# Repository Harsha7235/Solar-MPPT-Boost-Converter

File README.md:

Solar MPPT Boost Converter — 24 V Output
A hardware-oriented solar power conversion project involving the schematic design and PCB layout of an Arduino-assisted boost-converter stage. The design was created in KiCad and is intended to step up a lower DC input from a solar source to a nominal 24 V output.
Project status: Schematic and PCB design/fabrication work completed by the project author. The screenshots show the circuit schematic and routed PCB layout. Do not interpret the nominal output label as proof of a regulated 24 V output under every input/load condition; measured performance data should be added after testing.

Repository name
Solar-MPPT-Boost-Converter
Repository description
KiCad schematic and PCB design for an Arduino-assisted solar MPPT boost-converter prototype with a nominal 24 V output.
Project overview
The project combines a boost-converter power stage with a microcontroller-based control/monitoring arrangement. The visible schematic contains an Arduino Nano, an INA219 current/voltage-monitoring IC, an inductor, a Schottky power diode, a MOSFET switching device, input/output capacitors, and supporting gate/feedback components.

The intended system-level workflow is:
1. Accept a DC input from a solar source.
2. Use a boost power stage to raise the input voltage.
3. Use the Arduino-based control arrangement for the intended MPPT/control logic.
4. Monitor electrical quantities through the INA219 interface.
5. Provide a nominal 24 V output at the output connector.
Important: The supplied screenshots establish the circuit and PCB design elements, but do not show the complete MPPT firmware, a solar-panel test setup, calibration procedure, closed-loop control results, or measured efficiency. Add those details only when they are implemented and verified.
Hardware visible in the schematic
Reference / component	Value or part marking shown	Intended role
A1	Arduino Nano (V3.x footprint)	Microcontroller platform for control and monitoring
U1	INA219AD	I²C-based voltage/current/power monitoring
L1	220 µH	Boost-converter energy-storage inductor
D1	MBR1060	Schottky rectifier in the boost power stage
Q1	P30N06L	MOSFET switching device
C1, C2	470 µF	Bulk input/output filtering capacitors (confirm exact net placement from the schematic)
C3, C4	100 nF	High-frequency bypass/decoupling capacitors
R1	10 Ω	Gate-series resistor as drawn
R2	100 kΩ	Gate pull-down resistor as drawn
J1	2-pin connector	Input connection as labelled in the schematic
J2	2-pin connector	Output connection labelled VOUT_24V / GND
J3	2-pin connector	Additional board connection; verify its final intended use from the netlist

Part numbers and values above are transcribed from the provided schematic image. Confirm the exact manufacturer datasheets, pinouts, voltage/current ratings, capacitor polarity, and connector functions before applying power.
Design files
Upload the native KiCad project files to this repository so that the design can be inspected and edited:
- *.kicad_pro — KiCad project
- *.kicad_sch — schematic
- *.kicad_pcb — PCB layout
- fabrication/ — Gerber files, drill files, and fabrication notes (if generated)
- images/ — schematic and PCB screenshots
- firmware/ — Arduino source code (if available)
The screenshots alone are not a substitute for the editable KiCad source files or manufacturing outputs.
Design workflow
1. Schematic capture: Place the power-stage, sensing, controller, passive components, and connectors in KiCad.
2. Electrical connections: Connect the boost stage, sensing interface, controller pins, input, and output nets.
3. PCB placement: Arrange the components on the board while considering power-path length, switching-node area, grounding, and component accessibility.
4. Routing: Route the power and signal connections in the PCB editor. The supplied board image shows routed copper and the component footprints.
5. Fabrication preparation: Generate and inspect Gerber/drill outputs and verify the board against the schematic before manufacturing.
6. Bring-up and testing: Test with a current-limited bench supply and suitable load before connecting a solar panel or valuable equipment.
Power-electronics design considerations
A boost converter can produce an output voltage higher than its input, but the actual output depends on the input range, switching frequency, duty cycle, inductor, diode, MOSFET, load, feedback method, and losses.

For a practical MPPT implementation, document and validate:
- Solar-panel voltage/current operating range.
- MPPT algorithm used (for example, Perturb and Observe or Incremental Conductance), if implemented.
- PWM frequency and duty-cycle limits.
- Voltage/current sensing calibration and sampling rate.
- Output-voltage regulation method and over-voltage protection.
- Input undervoltage, output overcurrent, thermal, and short-circuit protection.
- Inductor saturation current, MOSFET safe operating area, diode rating, capacitor ripple-current rating, and PCB copper-current capacity.
The ideal continuous-conduction boost relationship is:
\[
V_{out} = \frac{V_{in}}{1-D}
\]
where D is the switch duty cycle. This is an ideal relationship, not a measured performance claim; real designs have losses and operating limits.
Safety and validation
This is a switching power-electronics circuit. Incorrect wiring, component polarity, PCB clearance, grounding, or control settings can damage hardware or cause burns/fire.

Before powering the board:
- Check the schematic-to-PCB consistency and run KiCad ERC and PCB DRC.
- Inspect solder joints, component orientation, connector polarity, and MOSFET/diode pinouts.
- Verify there are no shorts between input, output, and ground.
- Confirm the voltage ratings of all capacitors and semiconductors exceed the maximum possible circuit voltage with suitable margin.
- Start with a current-limited bench supply and a dummy load.
- Increase input voltage and load gradually while monitoring the MOSFET, diode, inductor, and capacitors for heating.
- Measure input voltage/current, output voltage/current, ripple, and efficiency before describing the converter as tested or regulated.
Do not connect the board directly to a battery, panel, or load until the design has passed these checks.
Results
The currently supplied project evidence is the KiCad schematic and PCB layout screenshots. Add a measured-results table here after bench testing:
Parameter	Measured result
Solar/DC input voltage range	To be measured
Input current	To be measured
Output voltage under load	To be measured
Output current / load	To be measured
Switching frequency	To be confirmed
Efficiency	To be measured
Output ripple	To be measured
Thermal performance	To be measured

Suggested repository structure
Solar-MPPT-Boost-Converter/
├── README.md
├── kicad/
│   ├── project.kicad_pro
│   ├── project.kicad_sch
│   └── project.kicad_pcb
├── fabrication/
│   ├── gerber/
│   └── drill/
├── firmware/
├── images/
│   ├── schematic.png
│   └── pcb-layout.png
└── docs/
    └── test-results.md
Author
P.Harsha Vardhan Reddy
B.Tech
AI & DS(CPS_S)
Amrita Vishwa Vidyapeetham, Coimbatore 

Designed and fabricated as a hands-on project in solar power electronics, embedded control, and PCB design.

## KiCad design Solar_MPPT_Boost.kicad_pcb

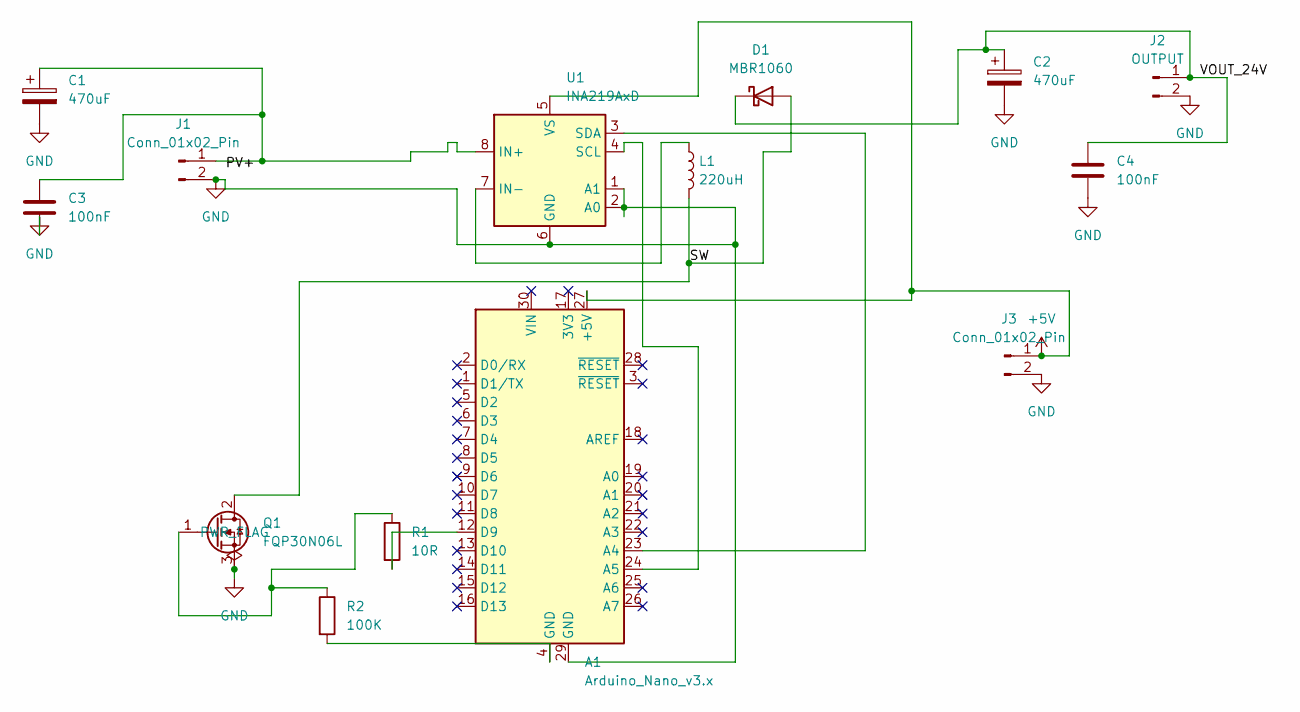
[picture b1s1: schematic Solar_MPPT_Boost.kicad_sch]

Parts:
A1: Arduino_Nano_v3.x; Arduino_Nano
C1, C2: 470uF; CP_Radial_D8.0mm_P3.50mm
C3, C4: 100nF; C_Disc_D5.0mm_W2.5mm_P5.00mm
D1: MBR1060; TO-220-2_Vertical
J1, J3: Conn_01x02_Pin; PinHeader_1x02_P2.54mm_Vertical
J2: OUTPUT; PinHeader_1x02_P2.54mm_Vertical
L1: 220uH; CP_Radial_D10.0mm_P5.00mm
Q1: FQP30N06L; TO-220-3_Vertical
R1: 10R; R_Axial_DIN0207_L6.3mm_D2.5mm_P10.16mm_Horizontal
R2: 100K; R_Axial_DIN0207_L6.3mm_D2.5mm_P10.16mm_Horizontal
U1: INA219AxD; SOIC-8_3.9x4.9mm_P1.27mm

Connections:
+5V: A1.27 (+5V), J3.1, U1.5 (VS)
/SW: D1.2 (A), L1.2, Q1.2 (D)
/VOUT_24V: C2.1, C4.1, D1.1 (K), J2.1
GND: A1.29 (GND), C1.2, C2.2, C3.2, C4.2, J1.2, J2.2, J3.2, Q1.3 (S), U1.1 (A1), U1.2 (A0), U1.6 (GND)
unnamed: A1.23 (A4), U1.3 (SDA)
unnamed: A1.24 (A5), U1.4 (SCL)
unnamed: A1.12 (D9), R1.2
unnamed: A1.4 (GND), R2.2
unnamed: C1.1, C3.1, J1.1, U1.8 (IN+)
unnamed: Q1.1 (G), R1.1, R2.1
unnamed: L1.1, U1.7 (IN-)

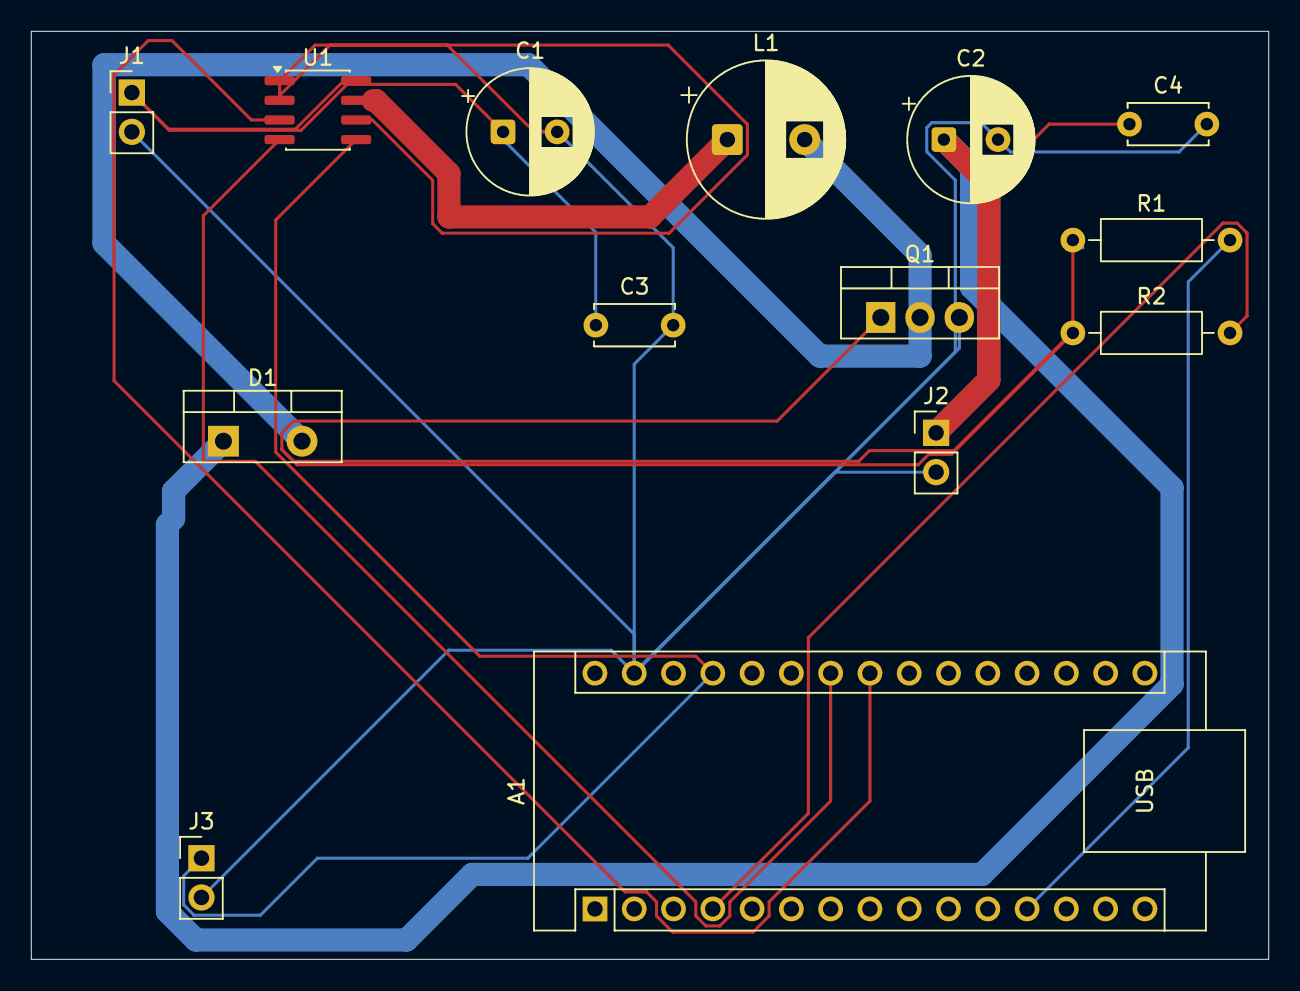
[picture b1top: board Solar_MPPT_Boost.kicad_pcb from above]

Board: 2 copper layers, 80.0 x 60.0 mm, 14 parts (0 on the bottom side), 11 nets.
